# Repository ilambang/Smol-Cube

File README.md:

# Smol-Cube
Smol Cube is an IoT Based remote Switch with IR Remote capabillity with AWS based serverless operation.

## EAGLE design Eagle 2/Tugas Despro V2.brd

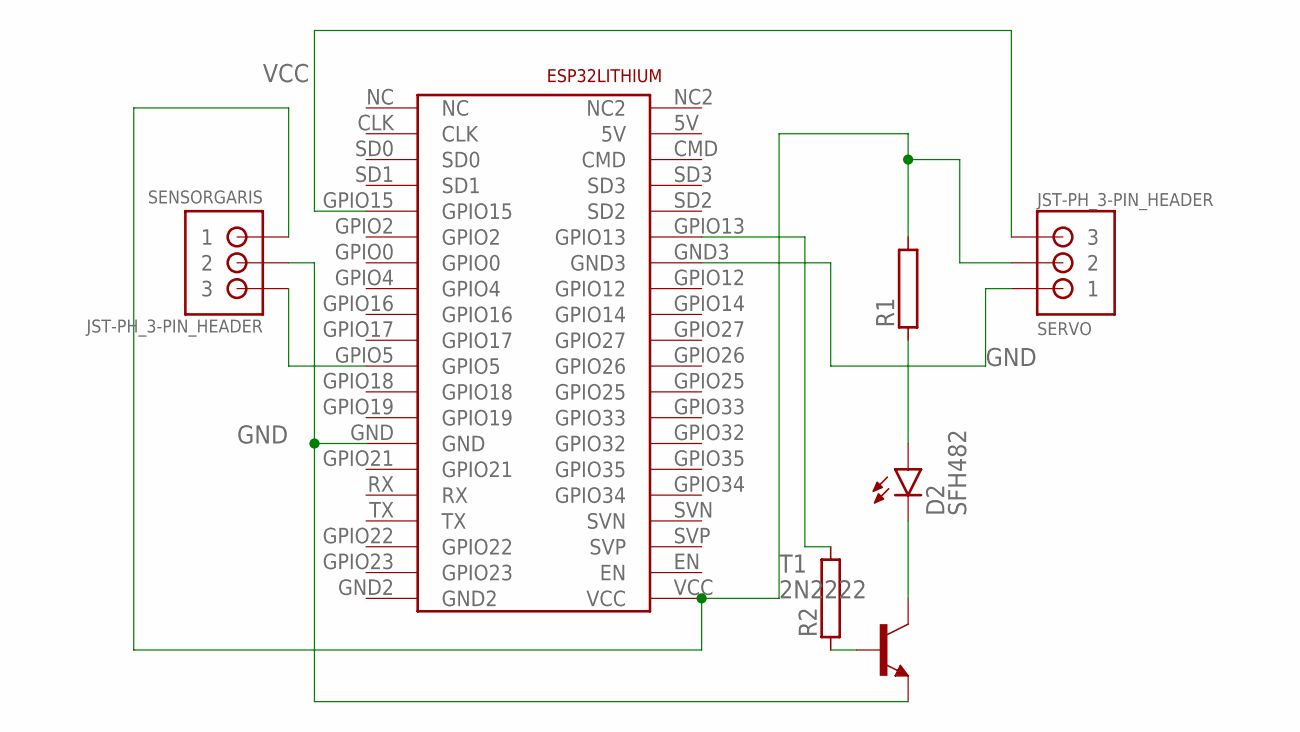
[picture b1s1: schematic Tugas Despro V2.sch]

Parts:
D2: SFH482
R1, R2: RAC01; AC01
SENSORGARIS: JST-PH_3-PIN_HEADER; JST_B3B-PH_HEADER
SERVO: JST-PH_3-PIN_HEADER; JST_B3B-PH_HEADER
T1: 2N2222; TO18
U$5: ESP32LITHIUM

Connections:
GND: SENSORGARIS.P2 (2), SERVO.P1 (1), T1.1 (E), U$5.GND, U$5.GND3
unnamed: SENSORGARIS.P3 (3), U$5.GPIO5
unnamed: SERVO.P3 (3), U$5.GPIO15
unnamed: R2.2, U$5.GPIO13
unnamed: R1.2, SERVO.P2 (2)
unnamed: D2.A, R1.1
unnamed: D2.K (C), T1.3 (C)
unnamed: R2.1, T1.2 (B)
VCC: SENSORGARIS.P1 (1), U$5.VCC

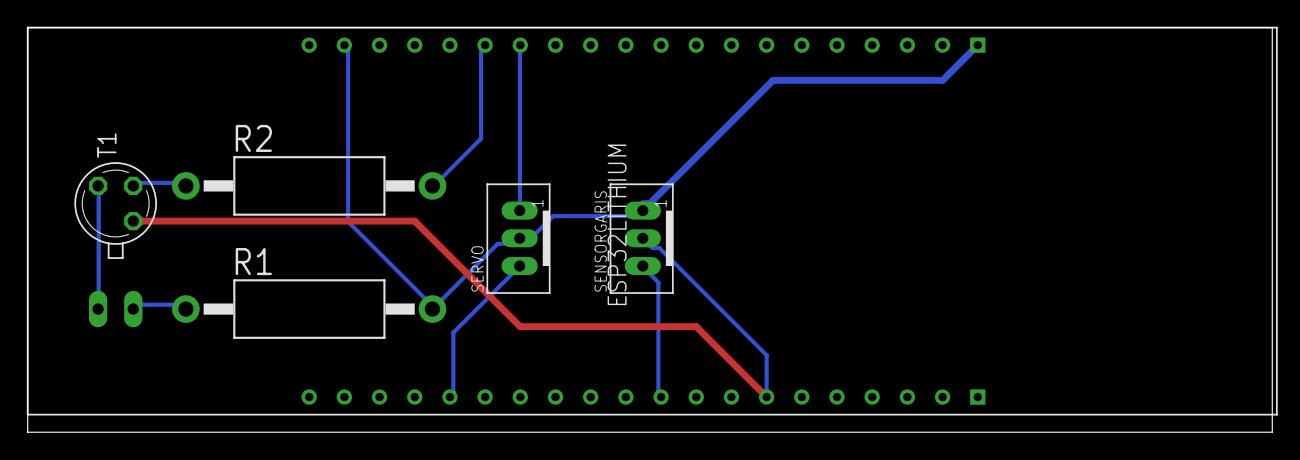
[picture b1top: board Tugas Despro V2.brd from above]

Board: 2 copper layers, 89.8 x 29.2 mm, 7 parts (1 on the bottom side), 9 nets.

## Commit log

2022-02-19 Update to latest repo: Latest ESP32 Program
2022-02-19 Added ESP2 Program
